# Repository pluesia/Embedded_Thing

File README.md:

# Mini Audio Spectrum

A tiny embedded system that allows to provide simple analysis of an audio signal, connected by a jack.

# Introduction
This project belongs to the course Embedded System Design (E7020E) of the 
LTU.

The repository contains all hardware blueprints, and the sources for building
a Spectometre with a STM32F4 microcontroller. The language used have been cargo.
The main purpose is to show all the sound frecuencies of a song in real time.
The audio input is given with a 3,5mm jack, and the output is shown in a 
LED 8x8 matrix, displaying the intensity of each band of frecuency.

# Authors
William Lindell (linwil-5@student.ltu.se)

Pablo Luesia (pablue-8@student.ltu.se)

# Build
It is neccesary to have stlink, openocd and cargo installed.
For building the code, it is necesary to go inside the cloned
folder, and execute:

```shell
cargo build --bin mini_audio_spectrum --features "hal rtfm"
````

The debug output can be done with ITM

# Work done
1. Hardware schematics and layout
2. Real board mount
3. Reset and reboot buttons 
4. Implemented in the code:
* PWM working with the TIM1 of the STM32F4 for the LED intensity
* ADC conversion working with interrupts for reading the audio input
* UART for showing the results for depuration

# Future work
Program the PCB with the binaries generated:
* PWM for modulating the LED intensity
* Generate frecuency extractor for ADC input
* Showing results in the LED matrix
* Use UART for configure the LED intensity
 
# Grades
## Grade 3 
 Sampling and show a simple interpretation of the audio signal.  
## Grade 4
 Understand and implement the fourier transform algorithm for the audio input.  
## Grade 5
 Add different modes of the display and the audio.

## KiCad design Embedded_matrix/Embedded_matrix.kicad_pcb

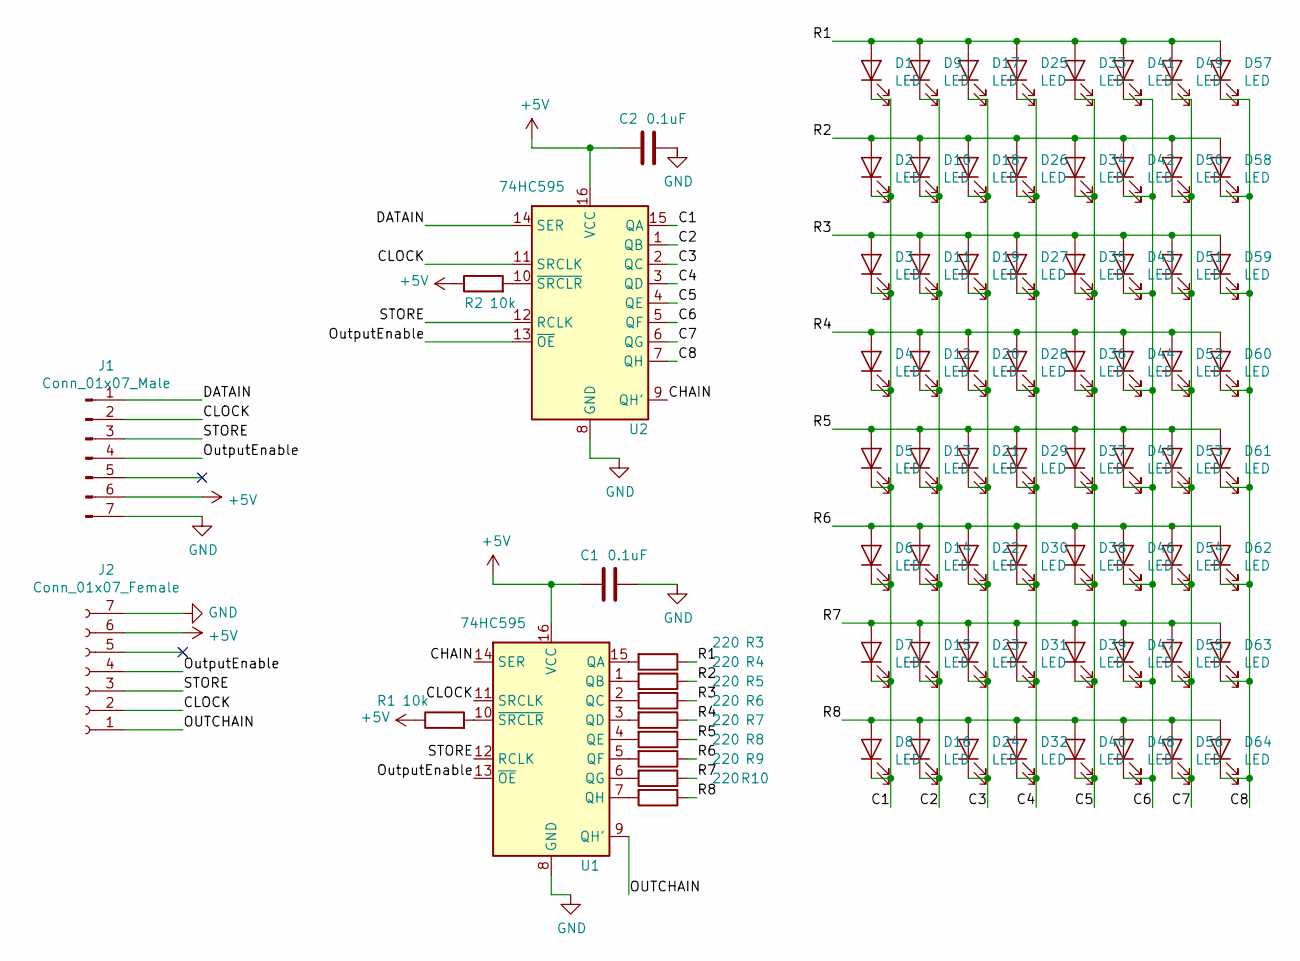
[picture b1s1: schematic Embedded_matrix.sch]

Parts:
C1, C2: 0.1uF; C_0805_2012Metric
D1, D2, D3, D4, D5, D6, D7, D8, D9, D10, D11, D12, D13, D14, D15, D16, D17, D18, D19, D20, D21, D22, D23, D24, D25, D26, D27, D28, D29, D30, D31, D32, D33, D34, D35, D36, D37, D38, D39, D40, D41, D42, D43, D44, D45, D46, D47, D48, D49, D50, D51, D52, D53, D54, D55, D56, D57, D58, D59, D60, D61, D62, D63, D64: LED; LED_D5.0mm
J1: Conn_01x07_Male; PinHeader_1x07_P2.54mm_Vertical
J2: Conn_01x07_Female; PinHeader_1x07_P2.54mm_Vertical
R1, R2: 10k; R_0805_2012Metric_Pad1.15x1.40mm_HandSolder
R3, R4, R5, R6, R7, R8, R9, R10: 220; R_0805_2012Metric_Pad1.15x1.40mm_HandSolder
U1, U2: 74HC595; DIP-16_W7.62mm_Socket

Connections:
+5V: C1.1, C2.1, J1.6, J2.6, R1.1, R2.1, U1.16 (VCC), U2.16 (VCC)
/C1: D1.1 (K), D2.1 (K), D3.1 (K), D4.1 (K), D5.1 (K), D6.1 (K), D7.1 (K), D8.1 (K), U2.15 (QA)
/C2: D9.1 (K), D10.1 (K), D11.1 (K), D12.1 (K), D13.1 (K), D14.1 (K), D15.1 (K), D16.1 (K), U2.1 (QB)
/C3: D17.1 (K), D18.1 (K), D19.1 (K), D20.1 (K), D21.1 (K), D22.1 (K), D23.1 (K), D24.1 (K), U2.2 (QC)
/C4: D25.1 (K), D26.1 (K), D27.1 (K), D28.1 (K), D29.1 (K), D30.1 (K), D31.1 (K), D32.1 (K), U2.3 (QD)
/C5: D33.1 (K), D34.1 (K), D35.1 (K), D36.1 (K), D37.1 (K), D38.1 (K), D39.1 (K), D40.1 (K), U2.4 (QE)
/C6: D41.1 (K), D42.1 (K), D43.1 (K), D44.1 (K), D45.1 (K), D46.1 (K), D47.1 (K), D48.1 (K), U2.5 (QF)
/C7: D49.1 (K), D50.1 (K), D51.1 (K), D52.1 (K), D53.1 (K), D54.1 (K), D55.1 (K), D56.1 (K), U2.6 (QG)
/C8: D57.1 (K), D58.1 (K), D59.1 (K), D60.1 (K), D61.1 (K), D62.1 (K), D63.1 (K), D64.1 (K), U2.7 (QH)
/CHAIN: U1.14 (SER), U2.9 (QH')
/CLOCK: J1.2, J2.2, U1.11 (SRCLK), U2.11 (SRCLK)
/DATAIN: J1.1, U2.14 (SER)
/OUTCHAIN: J2.1, U1.9 (QH')
/OutputEnable: J1.4, J2.4, U1.13 (~OE), U2.13 (~OE)
/R1: D1.2 (A), D9.2 (A), D17.2 (A), D25.2 (A), D33.2 (A), D41.2 (A), D49.2 (A), D57.2 (A), R3.1
/R2: D2.2 (A), D10.2 (A), D18.2 (A), D26.2 (A), D34.2 (A), D42.2 (A), D50.2 (A), D58.2 (A), R4.1
/R3: D3.2 (A), D11.2 (A), D19.2 (A), D27.2 (A), D35.2 (A), D43.2 (A), D51.2 (A), D59.2 (A), R5.1
/R4: D4.2 (A), D12.2 (A), D20.2 (A), D28.2 (A), D36.2 (A), D44.2 (A), D52.2 (A), D60.2 (A), R6.1
/R5: D5.2 (A), D13.2 (A), D21.2 (A), D29.2 (A), D37.2 (A), D45.2 (A), D53.2 (A), D61.2 (A), R7.1
/R6: D6.2 (A), D14.2 (A), D22.2 (A), D30.2 (A), D38.2 (A), D46.2 (A), D54.2 (A), D62.2 (A), R8.1
/R7: D7.2 (A), D15.2 (A), D23.2 (A), D31.2 (A), D39.2 (A), D47.2 (A), D55.2 (A), D63.2 (A), R9.1
/R8: D8.2 (A), D16.2 (A), D24.2 (A), D32.2 (A), D40.2 (A), D48.2 (A), D56.2 (A), D64.2 (A), R10.1
/STORE: J1.3, J2.3, U1.12 (RCLK), U2.12 (RCLK)
GND: C1.2, C2.2, J1.7, J2.7, U1.8 (GND), U2.8 (GND)
unnamed: R1.2, U1.10 (~SRCLR)
unnamed: R2.2, U2.10 (~SRCLR)
unnamed: R3.2, U1.15 (QA)
unnamed: R4.2, U1.1 (QB)
unnamed: R5.2, U1.2 (QC)
unnamed: R6.2, U1.3 (QD)
unnamed: R7.2, U1.4 (QE)
unnamed: R8.2, U1.5 (QF)
unnamed: R9.2, U1.6 (QG)
unnamed: R10.2, U1.7 (QH)

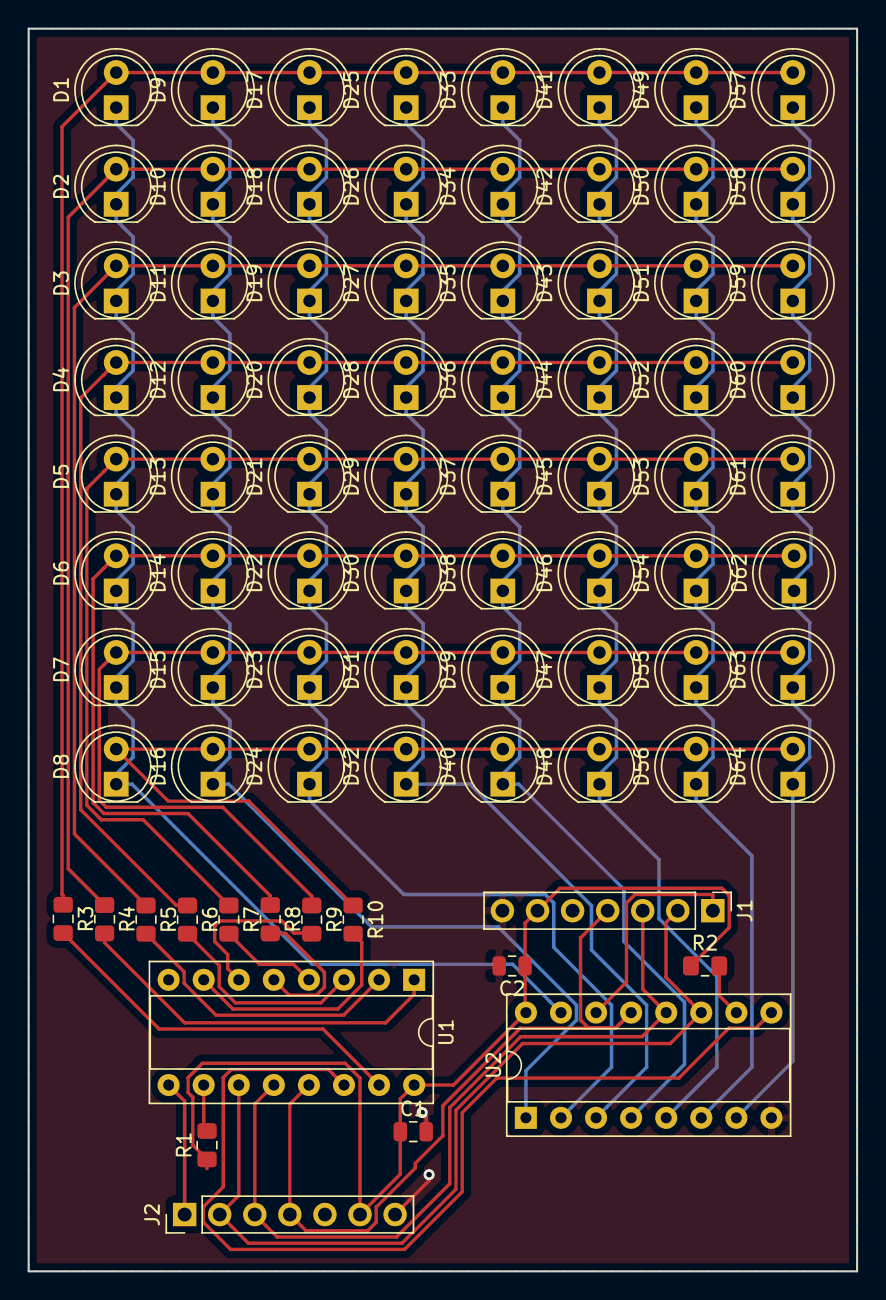
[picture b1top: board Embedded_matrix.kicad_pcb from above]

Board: 2 copper layers, 60.0 x 90.0 mm, 80 parts (0 on the bottom side), 34 nets.

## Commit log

2019-02-06 Adding layouts
2019-02-07 Created jack footprint
2019-02-08 added 7x5 footprint matrix
    Here is the footprint of 7x5 matrix, hope it is right
2019-02-08 Changed in the pins on the matrix
2019-02-12 Added jack
2019-02-13 Schematic for led matrix
    here is the schematic
2019-02-13 Added buttons
2019-02-13 Half of the control PCB blueprints added
2019-02-13 RIP matrix for now lets use leds
    updated
2019-02-13 Assigned PCB footprints
    Might be checked again to see they are in left in stock on sites
    led -> https://www.elfa.se/sv/led-groen-mm-rnd-components-rnd-135-00038/p/30100035?q=led&filter_advisor_answerPath=_0_1&filter_advisor_campaignId=559&page=16&origPos=16&origPageSize=50&simi=99.85
    -> capaictor -> https://www.elfa.se/en/ceramic-disk-capacitor-100-nf-50-vdc-mm-hitano-sf1h104z-l515b/p/16565659?q=*&filter_Category4=Ceramic+Disk+Capacitors&filter_Category3=Ceramic+Capacitors&filter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
    pin female --> https://www.elfa.se/en/pin-header-female-rnd-connect-rnd-205-00647/p/30093667?queryFromSuggest=true
    pin ma
2019-02-14 Finished control PCB. Generated greb files
2019-02-14 PCB made, might check, then gerber if not..
    Here is the PCB for the matrix pcb with 8x8 leds, the input pins and output pins looks the same but one will be with socket. Both female and male connector pins are the same according to the seller /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
    Pin size for male connector = Pin size for femlae connector.
    And the cupper traces could probably been better made x)
2019-02-14 Generated matrix gerber files
2019-02-14 Initial component list, added the matrix parts
    Here is all the components for the matrix
    list for the order
2019-02-15 Added shopping list
2019-02-15 Update README.md
    .
2019-02-15 Order List Done
    Added all the things to the order list see text link and column Mini Audio Spectrum for all the components. If wanted add more to the list
    just write them here then again in the google sheet. Don't forget to update the total amount of things / not specific amount just the types so it's easier to check the google if something is missing 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
2019-03-21 Cleared branch
2019-03-21 Generated gitignore
2019-03-21 Proyect generated
2019-03-23 added vscode tasks
2019-03-23 added cargo config
2019-03-26 Added documentation
2019-03-26 Working in analog read (ADC)
2019-03-26 It is possible to write in ADC registers
2019-03-27 Analog barely working
2019-03-27 ADC working and interrupting
2019-03-27 Added PWM file
2019-03-28 PWM done
2019-03-28 README modified for presentation
2019-03-28 Final Readme
2019-03-28 Src together
2019-03-28 Fixed course number
2019-03-28 modified openocd.cfg
2019-03-28 final addition
2019-03-28 Added Led intensity with uart
2019-04-01 Added button
